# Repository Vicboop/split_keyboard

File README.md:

# PCBLander

An Split keyboard. This is inspired in moonlander. It has 36 keys and its based on Nice!Nano V2 whit HotSwap for cherry KeySwitch. I got the inspiration and motivation after looking at so many cool designs so wanted to make one of my own.

## Features

72 keys

Wireless

ZMK Firmware

Hotswappable
## PCB

## BOM

| Product                | Quantity | Source     | Price (€) | Shipping (€) | Link |
|------------------------|----------|------------|-----------|--------------|------|
| Nice! Nano V2.0        | 2        | Aliexpress | 6,04      |              | https://pt.aliexpress.com/item/1005009516681283.html |
| Batery 3.7V 600mAh     | 2        | Aliexpress | 12,02     |              | https://pt.aliexpress.com/item/1005010194727026.html |
| White MX Hotswap       | 110      | Aliexpress | 16,66     |              | https://pt.aliexpress.com/item/1005005090520759.html |
| Akko Crystal V3 Switch | 80       | Aliexpress | 31,66     |              | https://pt.aliexpress.com/item/1005008942995452.html |
| PCB                    | 1        | JLCPCB     | 28,40     | 19,79        |      |
| Diode 1N4148W          | 100      | Aliexpress | 1,69      |              | https://pt.aliexpress.com/item/1005007903085825.html |
| **Total**              |          |            | **112,05**|              |      |

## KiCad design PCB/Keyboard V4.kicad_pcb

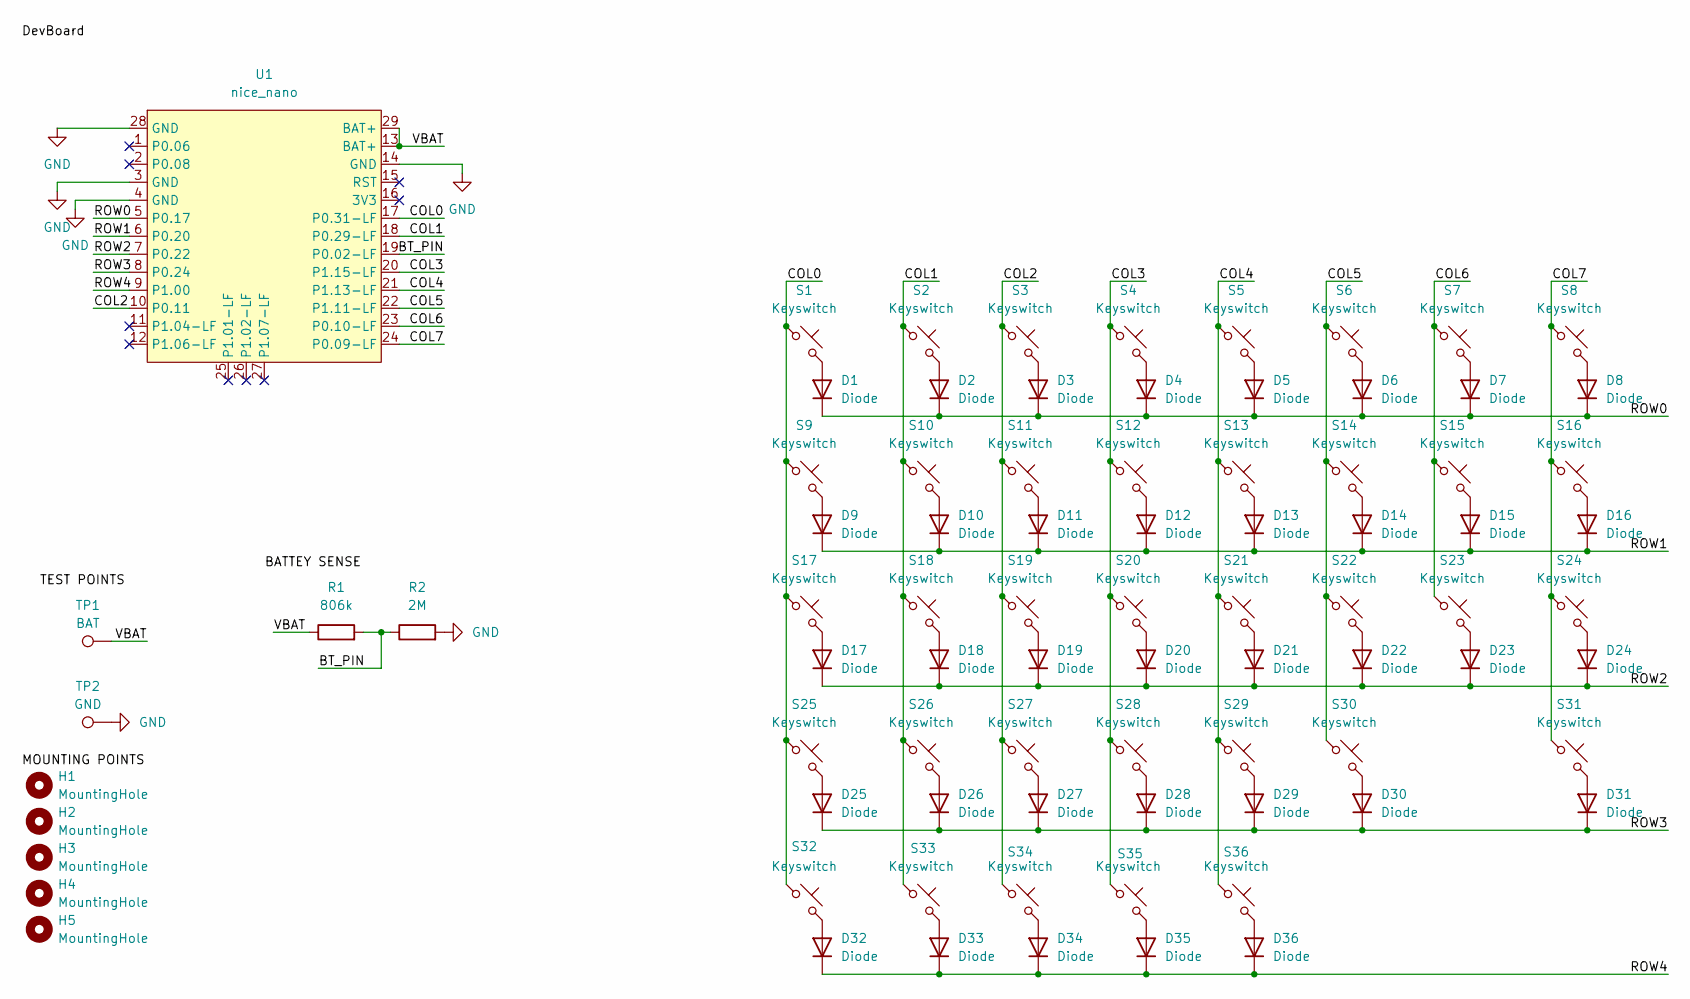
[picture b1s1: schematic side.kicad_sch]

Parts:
D1, D2, D3, D4, D5, D6, D7, D8, D9, D10, D11, D12, D13, D14, D15, D16, D17, D18, D19, D20, D21, D22, D23, D24, D25, D26, D27, D28, D29, D30, D31, D32, D33, D34, D35, D36: Diode; D_SOD-123
H1, H2, H3, H4, H5: MountingHole; MouseBite-Slot_2.54x5.08mm_on-edge_D0.5mm_P0.85mm_5h_Trace
R1: 806k; R_0805_2012Metric
R2: 2M; R_0805_2012Metric
S1, S2, S3, S4, S5, S6, S7, S8, S9, S10, S11, S12, S13, S14, S15, S16, S17, S18, S19, S20, S21, S22, S23, S24, S25, S26, S27, S28, S29, S30, S31, S32, S33, S34, S35, S36: Keyswitch; Hotswap_MX_1.00u
TP1: BAT; TestPoint_Pad_D2.0mm
TP2: GND; TestPoint_Pad_D2.0mm
U1: nice_nano; nice_nano_AH_USBup

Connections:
/Right/BT_PIN: R1.2, R2.1, U1.19 (P0.02-LF)
/Right/COL0: S1.1, S9.1, S17.1, S25.1, S32.1, U1.17 (P0.31-LF)
/Right/COL1: S2.1, S10.1, S18.1, S26.1, S33.1, U1.18 (P0.29-LF)
/Right/COL2: S3.1, S11.1, S19.1, S27.1, S34.1, U1.10 (P0.11)
/Right/COL3: S4.1, S12.1, S20.1, S28.1, S35.1, U1.20 (P1.15-LF)
/Right/COL4: S5.1, S13.1, S21.1, S29.1, S36.1, U1.21 (P1.13-LF)
/Right/COL5: S6.1, S14.1, S22.1, S30.1, U1.22 (P1.11-LF)
/Right/COL6: S7.1, S15.1, S23.1, U1.23 (P0.10-LF)
/Right/COL7: S8.1, S16.1, S24.1, S31.1, U1.24 (P0.09-LF)
/Right/ROW0: D1.1 (K), D2.1 (K), D3.1 (K), D4.1 (K), D5.1 (K), D6.1 (K), D7.1 (K), D8.1 (K), U1.5 (P0.17)
/Right/ROW1: D9.1 (K), D10.1 (K), D11.1 (K), D12.1 (K), D13.1 (K), D14.1 (K), D15.1 (K), D16.1 (K), U1.6 (P0.20)
/Right/ROW2: D17.1 (K), D18.1 (K), D19.1 (K), D20.1 (K), D21.1 (K), D22.1 (K), D23.1 (K), D24.1 (K), U1.7 (P0.22)
/Right/ROW3: D25.1 (K), D26.1 (K), D27.1 (K), D28.1 (K), D29.1 (K), D30.1 (K), D31.1 (K), U1.8 (P0.24)
/Right/ROW4: D32.1 (K), D33.1 (K), D34.1 (K), D35.1 (K), D36.1 (K), U1.9 (P1.00)
GND: R2.2, TP2.1, U1.3 (GND), U1.4 (GND), U1.14 (GND), U1.28 (GND); also elsewhere on the board
unnamed: D1.2 (A), S1.2
unnamed: D2.2 (A), S2.2
unnamed: D3.2 (A), S3.2
unnamed: D4.2 (A), S4.2
unnamed: D5.2 (A), S5.2
unnamed: D6.2 (A), S6.2
unnamed: D7.2 (A), S7.2
unnamed: D8.2 (A), S8.2
unnamed: D9.2 (A), S9.2
unnamed: D10.2 (A), S10.2
unnamed: D11.2 (A), S11.2
unnamed: D12.2 (A), S12.2
unnamed: D13.2 (A), S13.2
unnamed: D14.2 (A), S14.2
unnamed: D15.2 (A), S15.2
unnamed: D16.2 (A), S16.2
unnamed: D17.2 (A), S17.2
unnamed: D18.2 (A), S18.2
unnamed: D19.2 (A), S19.2
unnamed: D20.2 (A), S20.2
unnamed: D21.2 (A), S21.2
unnamed: D22.2 (A), S22.2
unnamed: D23.2 (A), S23.2
unnamed: D24.2 (A), S24.2
unnamed: D25.2 (A), S25.2
unnamed: D26.2 (A), S26.2
unnamed: D27.2 (A), S27.2
unnamed: D28.2 (A), S28.2
unnamed: D29.2 (A), S29.2
unnamed: D30.2 (A), S30.2
unnamed: D31.2 (A), S31.2
unnamed: D32.2 (A), S32.2
unnamed: D33.2 (A), S33.2
unnamed: D34.2 (A), S34.2
unnamed: D35.2 (A), S35.2
unnamed: D36.2 (A), S36.2
unnamed 103: U1.15 (RST); also elsewhere on the board

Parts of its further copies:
D37, D38, D39, D40, D41, D42, D43, D44, D45, D46, D47, D48, D49, D50, D51, D52, D53, D54, D55, D56, D57, D58, D59, D60, D61, D62, D63, D64, D65, D66, D67, D68, D69, D70, D71, D72: Diode; D_SOD-123
R3: 806k; R_0805_2012Metric
R4: 2M; R_0805_2012Metric
S37, S38, S39, S40, S41, S42, S43, S44, S45, S46, S47, S48, S49, S50, S51, S52, S53, S54, S55, S56, S57, S58, S59, S60, S61, S62, S63, S64, S65, S66, S67, S68, S69, S70, S71, S72: Keyswitch; Hotswap_MX_1.00u
TP3: BAT; TestPoint_Pad_D2.0mm
TP4: GND; TestPoint_Pad_D2.0mm
U2: nice_nano; nice_nano_AH_USBup

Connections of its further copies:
/Left/BT_PIN: R3.2, R4.1, U2.19 (P0.02-LF)
/Left/COL0: S37.1, S45.1, S53.1, S61.1, S68.1, U2.17 (P0.31-LF)
/Left/COL1: S38.1, S46.1, S54.1, S62.1, S69.1, U2.18 (P0.29-LF)
/Left/COL2: S39.1, S47.1, S55.1, S63.1, S70.1, U2.10 (P0.11)
/Left/COL3: S40.1, S48.1, S56.1, S64.1, S71.1, U2.20 (P1.15-LF)
/Left/COL4: S41.1, S49.1, S57.1, S65.1, S72.1, U2.21 (P1.13-LF)
/Left/COL5: S42.1, S50.1, S58.1, S66.1, U2.22 (P1.11-LF)
/Left/COL6: S43.1, S51.1, S59.1, U2.23 (P0.10-LF)
/Left/COL7: S44.1, S52.1, S60.1, S67.1, U2.24 (P0.09-LF)
/Left/ROW0: D37.1 (K), D38.1 (K), D39.1 (K), D40.1 (K), D41.1 (K), D42.1 (K), D43.1 (K), D44.1 (K), U2.5 (P0.17)
/Left/ROW1: D45.1 (K), D46.1 (K), D47.1 (K), D48.1 (K), D49.1 (K), D50.1 (K), D51.1 (K), D52.1 (K), U2.6 (P0.20)
/Left/ROW2: D53.1 (K), D54.1 (K), D55.1 (K), D56.1 (K), D57.1 (K), D58.1 (K), D59.1 (K), D60.1 (K), U2.7 (P0.22)
/Left/ROW3: D61.1 (K), D62.1 (K), D63.1 (K), D64.1 (K), D65.1 (K), D66.1 (K), D67.1 (K), U2.8 (P0.24)
/Left/ROW4: D68.1 (K), D69.1 (K), D70.1 (K), D71.1 (K), D72.1 (K), U2.9 (P1.00)
/Left/VBAT: R3.1, TP3.1; also elsewhere on the board
GND: R4.2, TP4.1, U2.3 (GND), U2.4 (GND), U2.14 (GND), U2.28 (GND); also elsewhere on the board
unnamed: D37.2 (A), S37.2
unnamed: D38.2 (A), S38.2
unnamed: D39.2 (A), S39.2
unnamed: D40.2 (A), S40.2
unnamed: D41.2 (A), S41.2
unnamed: D42.2 (A), S42.2
unnamed: D43.2 (A), S43.2
unnamed: D44.2 (A), S44.2
unnamed: D45.2 (A), S45.2
unnamed: D46.2 (A), S46.2
unnamed: D47.2 (A), S47.2
unnamed: D48.2 (A), S48.2
unnamed: D49.2 (A), S49.2
unnamed: D50.2 (A), S50.2
unnamed: D51.2 (A), S51.2
unnamed: D52.2 (A), S52.2
unnamed: D53.2 (A), S53.2
unnamed: D54.2 (A), S54.2
unnamed: D55.2 (A), S55.2
unnamed: D56.2 (A), S56.2
unnamed: D57.2 (A), S57.2
unnamed: D58.2 (A), S58.2
unnamed: D59.2 (A), S59.2
unnamed: D60.2 (A), S60.2
unnamed: D61.2 (A), S61.2
unnamed: D62.2 (A), S62.2
unnamed: D63.2 (A), S63.2
unnamed: D64.2 (A), S64.2
unnamed: D65.2 (A), S65.2
unnamed: D66.2 (A), S66.2
unnamed: D67.2 (A), S67.2
unnamed: D68.2 (A), S68.2
unnamed: D69.2 (A), S69.2
unnamed: D70.2 (A), S70.2
unnamed: D71.2 (A), S71.2
unnamed: D72.2 (A), S72.2
unnamed 102: U2.13 (BAT+), U2.29 (BAT+); also elsewhere on the board
unnamed 104: U2.15 (RST); also elsewhere on the board

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
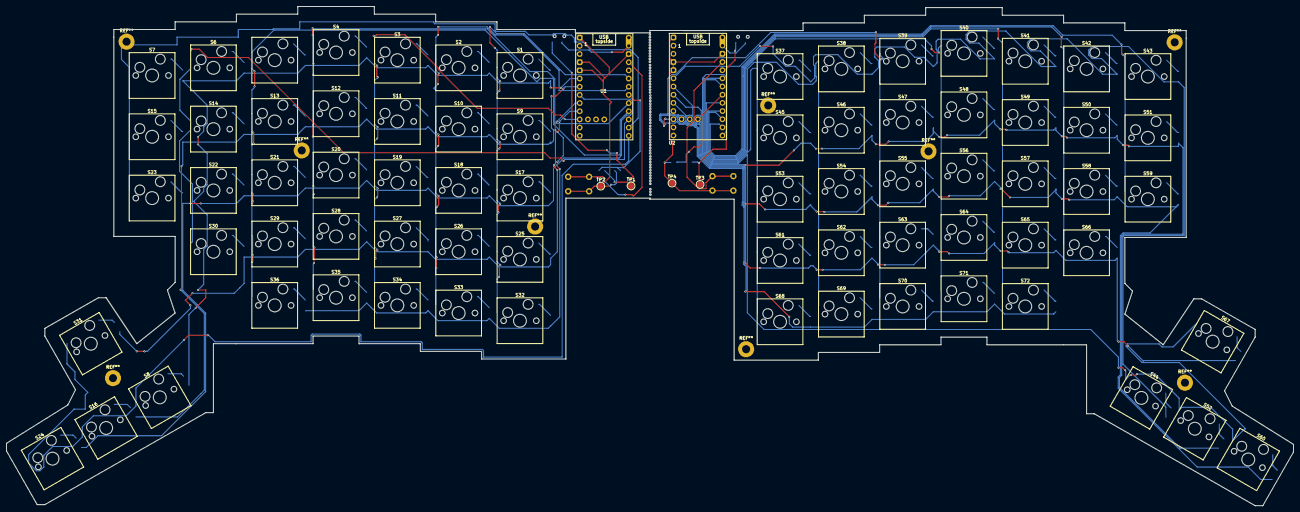
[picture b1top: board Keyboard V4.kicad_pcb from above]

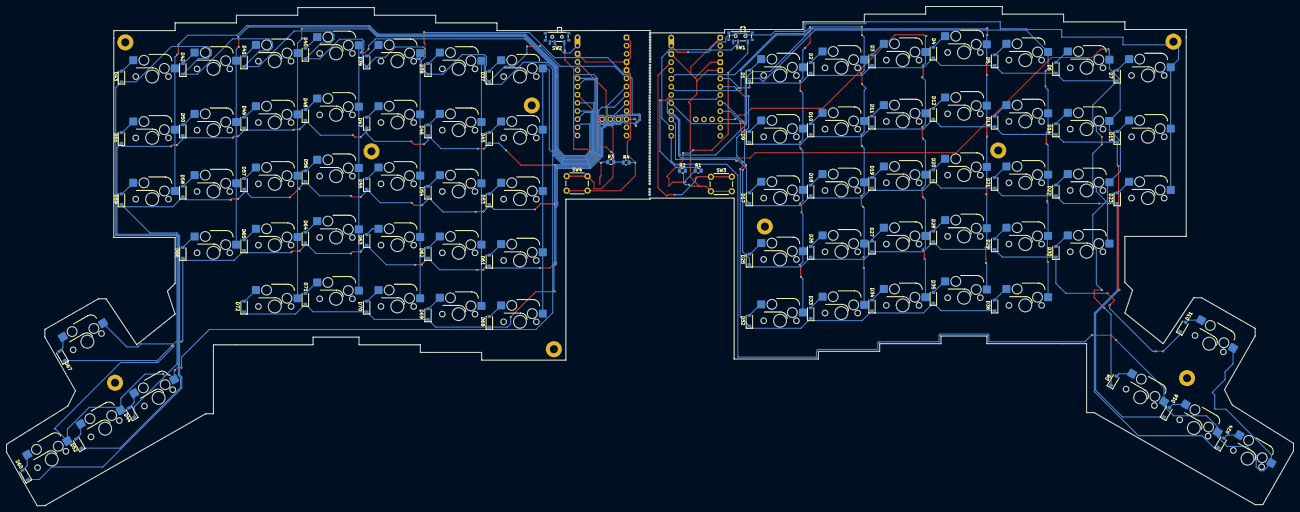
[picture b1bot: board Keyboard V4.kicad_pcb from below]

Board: 2 copper layers, 399.9 x 155.1 mm, 158 parts (80 on the bottom side), 107 nets.

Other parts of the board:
SW1, SW2: SW_SPDT; SW_SPDT_PCM12
SW3, SW4: SW_Push; SW_PUSH_6mm

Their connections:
/Left/VBAT: SW2.1 (A); also elsewhere on the board
GND: SW3.2, SW4.2; also elsewhere on the board
unnamed 102: SW2.2 (B); also elsewhere on the board
unnamed 103: SW3.1; also elsewhere on the board
unnamed 104: SW4.1; also elsewhere on the board

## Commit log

2025-10-26 Update README with image and keyboard description
    Added an image and a brief description of the keyboard.
2025-10-26 Update README with project dependencies and image
2025-10-26 Enhance keyboard description with HotSwap feature
    Updated the description of the keyboard to include HotSwap feature.
2026-03-06 Enhance README with project details and image
    Added project description and PCB image to README.
2026-03-06 Add image of the keyboard PCB to README
    Added an image to the README for visual reference.
2026-03-06 Fix typo in keyboard description
    Corrected a typo in the keyboard description.
2026-03-06 Update README with PCB images
    Added images for left and right PCB views.
2026-03-06 Add BOM section to README
    Added BOM section with total cost information.
2026-03-07 Rename keyboardv3_left-nice_nano_v2-zmk.uf2 to firmware/keyboardv3_left-nice_nano_v2-zmk.uf2
2026-03-07 Rename keyboardv3_right-nice_nano_v2-zmk.uf2 to firmware/keyboardv3_right-nice_nano_v2-zmk.uf2
2026-03-07 Rename Keyboard V4.kicad_prl to PCB/Keyboard V4.kicad_prl
2026-03-07 Rename Keyboard V4.kicad_pro to PCB/Keyboard V4.kicad_pro
2026-03-13 Revise BOM with product information and totals
    Updated BOM table with product details and prices.
2026-06-02 Add ZMK firmware with Studio support
2026-06-02 Pin ZMK to v0.3
2026-06-02 Fix physical layout negative rotation syntax
2026-06-02 Fix mirrored matrix transform
